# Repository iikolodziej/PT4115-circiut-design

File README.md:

# PT4115-circiut-design
PT4115_circiut_design 30V, 1.2A Step-down High Brightness LED Driver with 5000:1 Dimming

## Introduction
I need some drivers for my another project with UV leds, so here were are ;)

### Tools and others

# Gallery
## Schematic and board design created in Autodesk Eagle:

## Self made PCB's

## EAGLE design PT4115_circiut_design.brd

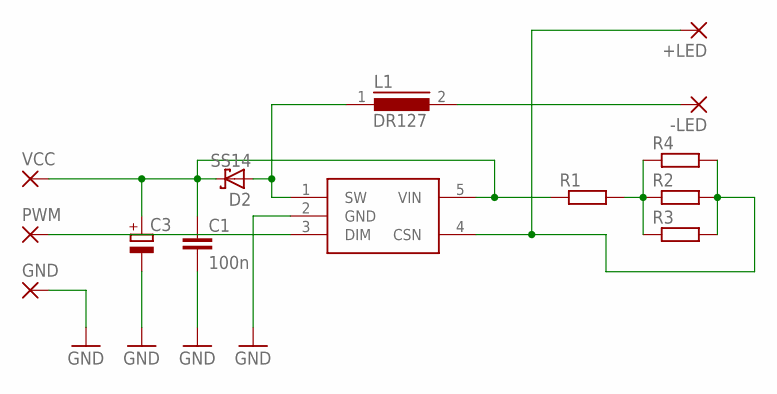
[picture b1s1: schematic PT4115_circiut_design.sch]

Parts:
+LED: SMD5; SMD2,54-5,08
-LED: SMD5; SMD2,54-5,08
C1: 100n; C0805
C3: CPOL-EUSMCD; SMC_D
D2: SS14; DO-214AC
GND: SMD5; SMD2,54-5,08
L1: DR127
PWM: SMD5; SMD2,54-5,08
R1, R2, R3, R4: R-EU_M0805; M0805
U$1: PT4115; SOT-89-5
VCC: SMD5; SMD2,54-5,08

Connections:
GND: C1.2, C3.-, GND.1, U$1.2 (GND)
unnamed: PWM.1, U$1.3 (DIM)
unnamed: C1.1, C3.+, D2.K, R1.1, U$1.5 (VIN), VCC.1
unnamed: D2.A, L1.1, U$1.1 (SW)
unnamed: -LED.1, L1.2
unnamed: +LED.1, R2.2, R3.2, R4.2, U$1.4 (CSN)
unnamed: R1.2, R2.1, R3.1, R4.1

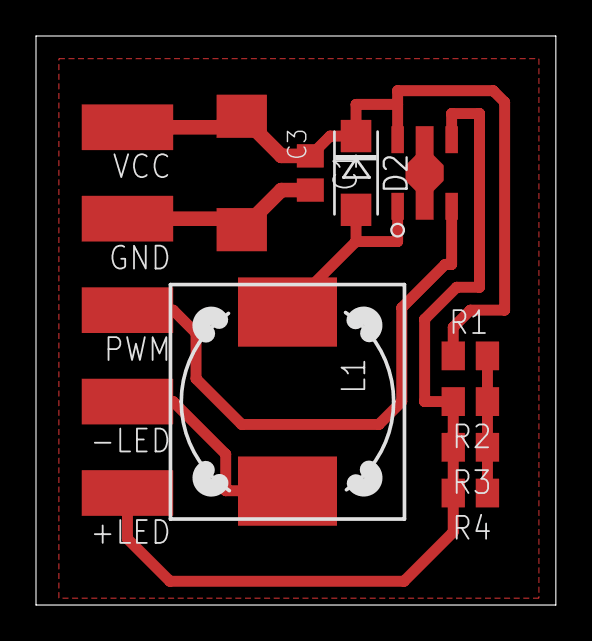
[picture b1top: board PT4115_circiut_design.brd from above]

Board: 2 copper layers, 28.9 x 31.6 mm, 14 parts (0 on the bottom side), 7 nets.

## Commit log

2023-10-19 Adding design files
